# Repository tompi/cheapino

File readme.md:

Cheapino
========

Probably one of the cheapest split keyboards you can build.

This is the result of really enjoying building keyboards,
but not wanting to spend that much money on it.
The pcb is reversible, connected using rj45,
and utilizes a japanese duplex matrix, so only one
mcu is needed. For hotswap I recommend a case(pictured above),
but soldering the switches is of course the cheapest option :)

You want one?
See the [ordering guide](doc/orderingguide.md) for what you need and how to buy it.

See the [build guide v2](doc/buildguide_v2.md) for more details and pictures of how to actually build it.

Some info on the [plate/case solutions](doc/plates_and_cases.md) I know about.

Checkout the [troubleshooting guide](doc/troubleshooting.md) if your Cheapino does not work.

See the [firmware guide](doc/firmware.md) for how to build and customize keyboard firmware.
The cheapino has vial support, or you can build your own QMK to customize EVERYTHING.
Even the onboard RP2040-Zero LED is controllable by QMK...

I added [a few tips and tricks here](doc/tips.md).

[Loads of beautiful build pictures here.](doc/gallery.md)

# License

This work is licensed under a [Creative Commons Attribution license.](LICENSE.txt)

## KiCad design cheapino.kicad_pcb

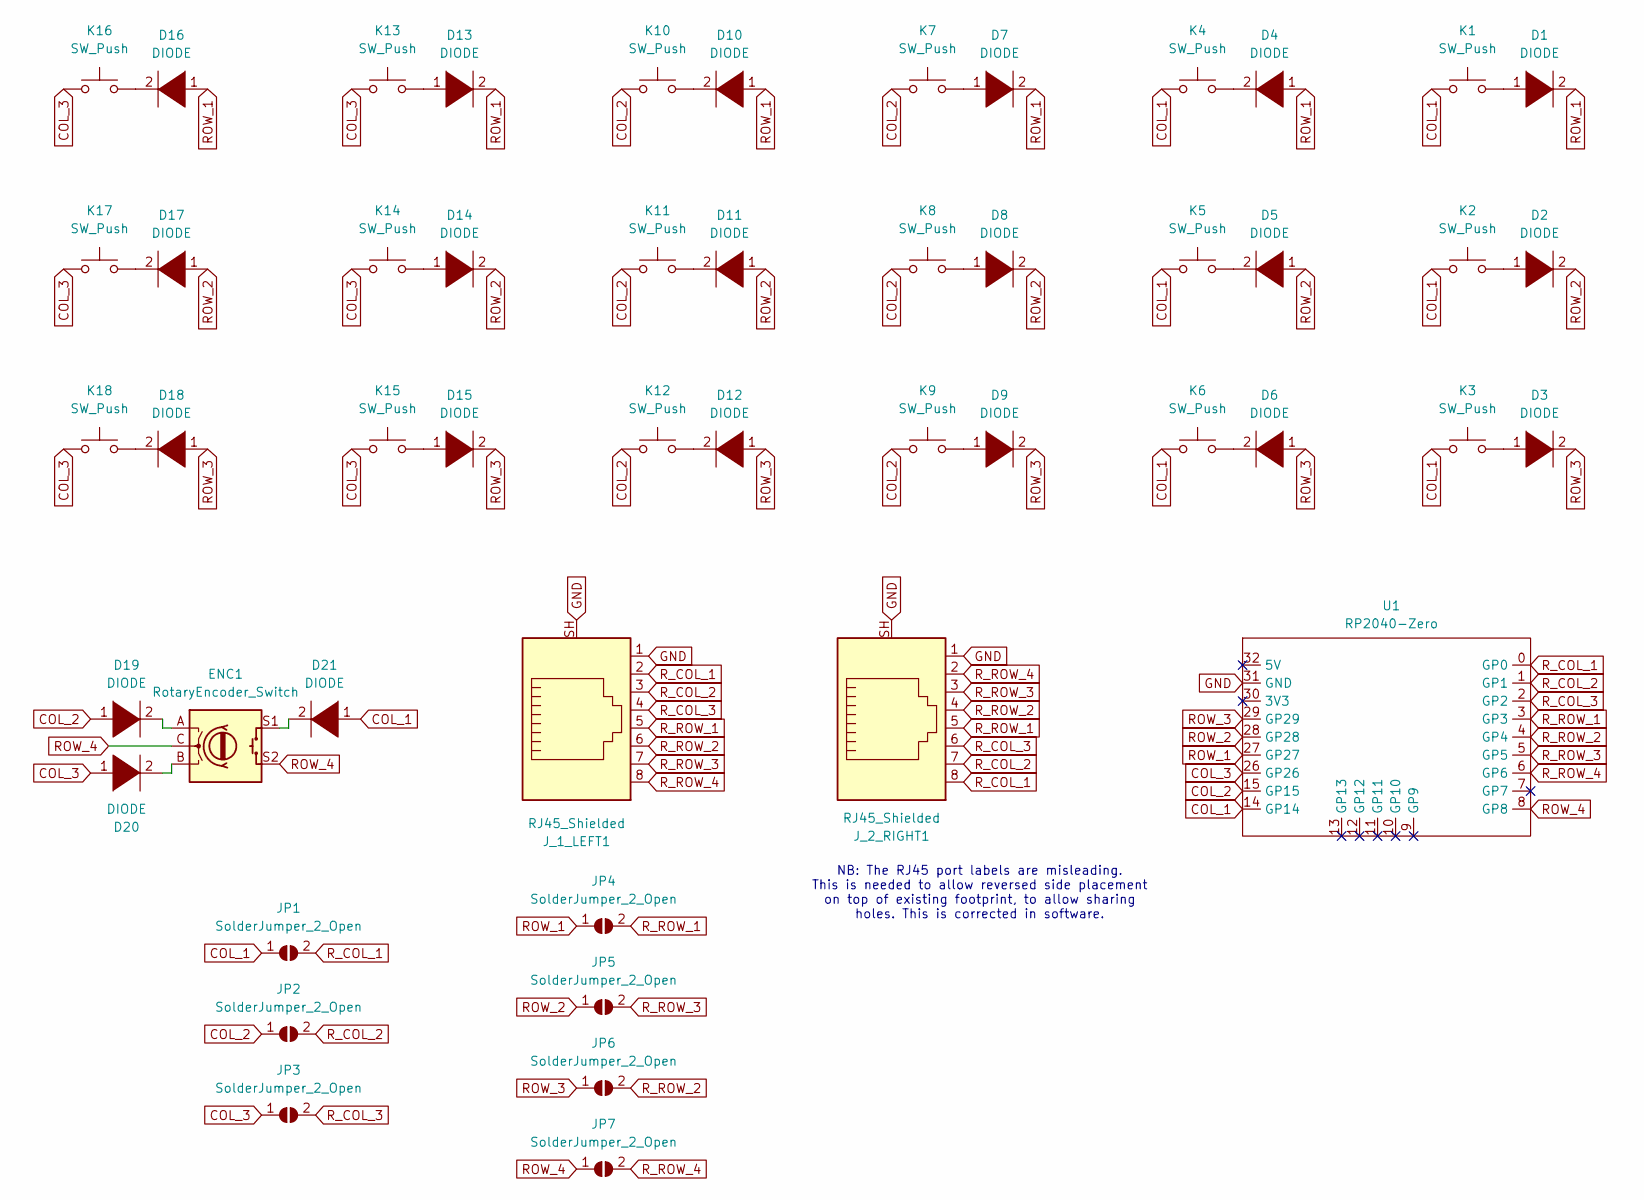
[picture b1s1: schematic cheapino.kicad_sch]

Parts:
D1, D2, D3, D4, D5, D6, D7, D8, D9, D10, D11, D12, D13, D14, D15, D17, D18, D19, D20, D21: DIODE; Diode-dual
D16: DIODE; D_SOD123_axial
ENC1: RotaryEncoder_Switch; RotaryEncoder_Alps_EC11E-Switch_Vertical_H20mm
JP1, JP2, JP3, JP4, JP5, JP6, JP7: SolderJumper_2_Open; SolderJumper-2_P1.3mm_Open_TrianglePad1.0x1.5mm
J_1_LEFT1, J_2_RIGHT1: RJ45_Shielded; RJ45_Ninigi_GE
K1, K2, K3, K4, K5, K6, K7, K8, K9, K10, K11, K12, K13, K14, K15, K16, K17, K18: SW_Push; Kailh_socket_MX_optional_reversible
U1: RP2040-Zero; MCU_RP2040_Zero_34

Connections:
COL_1: D21.1 (K), JP1.1 (A), K1.1, K2.1, K3.1, K4.1, K5.1, K6.1, U1.14 (GP14)
COL_2: D19.1 (K), JP2.1 (A), K7.1, K8.1, K9.1, K10.1, K11.1, K12.1, U1.15 (GP15)
COL_3: D20.1 (K), JP3.1 (A), K13.1, K14.1, K15.1, K16.1, K17.1, K18.1, U1.26 (GP26)
GND: J_1_LEFT1.1, J_1_LEFT1.SH, J_2_RIGHT1.1, J_2_RIGHT1.SH, U1.31 (GND)
unnamed: D1.1 (K), K1.2
unnamed: D2.1 (K), K2.2
unnamed: D3.1 (K), K3.2
unnamed: D4.2 (A), K4.2
unnamed: D5.2 (A), K5.2
unnamed: D6.2 (A), K6.2
unnamed: D7.1 (K), K7.2
unnamed: D8.1 (K), K8.2
unnamed: D9.1 (K), K9.2
unnamed: D10.2 (A), K10.2
unnamed: D11.2 (A), K11.2
unnamed: D12.2 (A), K12.2
unnamed: D13.1 (K), K13.2
unnamed: D14.1 (K), K14.2
unnamed: D15.1 (K), K15.2
unnamed: D16.2 (A), K16.2
unnamed: D17.2 (A), K17.2
unnamed: D18.2 (A), K18.2
unnamed: D19.2 (A), ENC1.A
unnamed: D20.2 (A), ENC1.B
unnamed: D21.2 (A), ENC1.S1
ROW_1: D1.2 (A), D4.1 (K), D7.2 (A), D10.1 (K), D13.2 (A), D16.1 (K), JP4.1 (A), U1.27 (GP27)
ROW_2: D2.2 (A), D5.1 (K), D8.2 (A), D11.1 (K), D14.2 (A), D17.1 (K), JP5.1 (A), U1.28 (GP28)
ROW_3: D3.2 (A), D6.1 (K), D9.2 (A), D12.1 (K), D15.2 (A), D18.1 (K), JP6.1 (A), U1.29 (GP29)
ROW_4: ENC1.C, ENC1.S2, JP7.1 (A), U1.8 (GP8)
R_COL_1: JP1.2 (B), J_1_LEFT1.2, J_2_RIGHT1.8, U1.0 (GP0)
R_COL_2: JP2.2 (B), J_1_LEFT1.3, J_2_RIGHT1.7, U1.1 (GP1)
R_COL_3: JP3.2 (B), J_1_LEFT1.4, J_2_RIGHT1.6, U1.2 (GP2)
R_ROW_1: JP4.2 (B), J_1_LEFT1.5, J_2_RIGHT1.5, U1.3 (GP3)
R_ROW_2: JP6.2 (B), J_1_LEFT1.6, J_2_RIGHT1.4, U1.4 (GP4)
R_ROW_3: JP5.2 (B), J_1_LEFT1.7, J_2_RIGHT1.3, U1.5 (GP5)
R_ROW_4: JP7.2 (B), J_1_LEFT1.8, J_2_RIGHT1.2, U1.6 (GP6)

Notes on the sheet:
NB: The RJ45 port labels are misleading. This is needed to allow reversed side placement on top of existing footprint, to allow sharing holes. This is corrected in software.

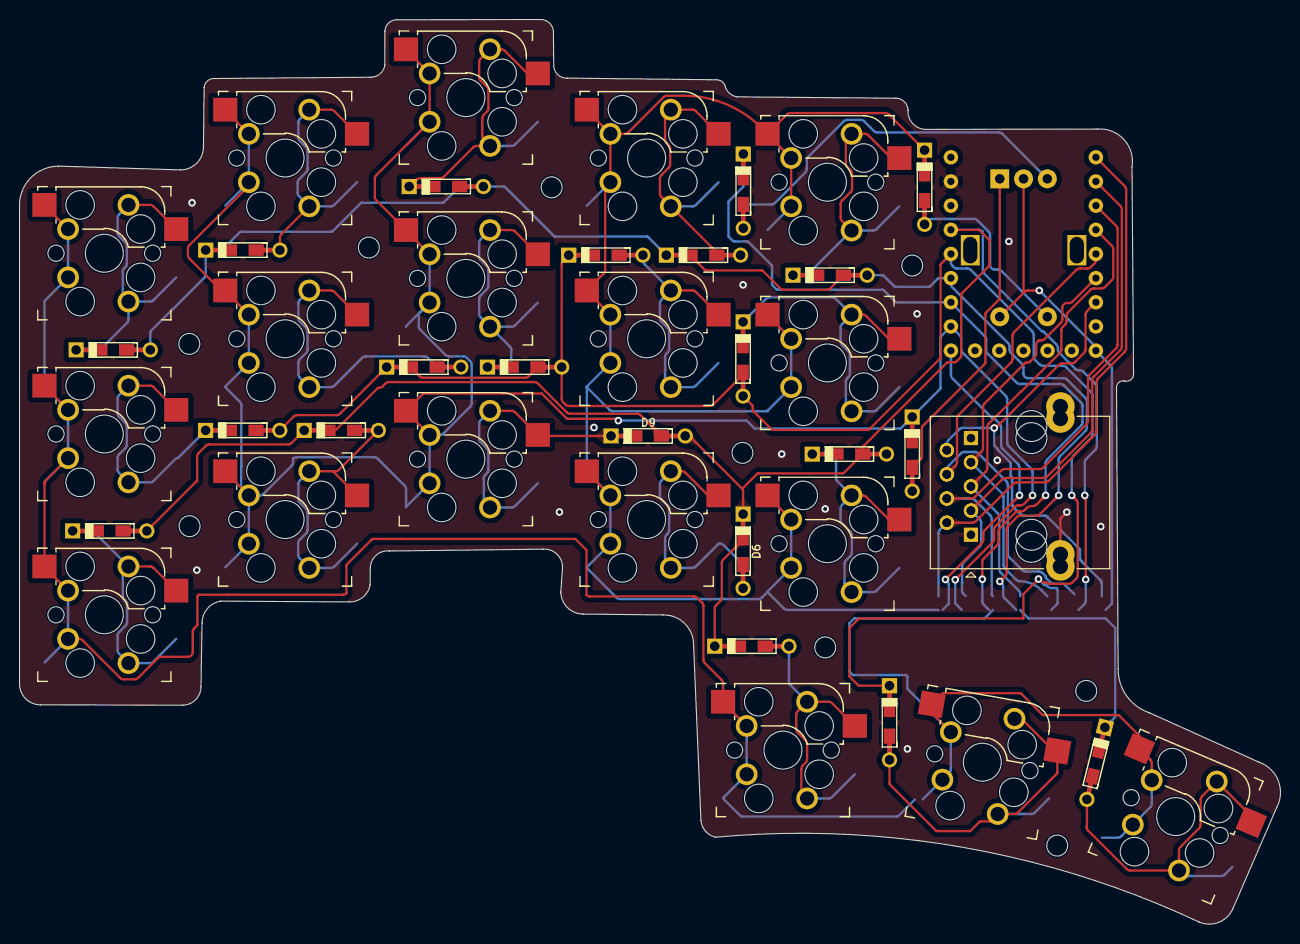
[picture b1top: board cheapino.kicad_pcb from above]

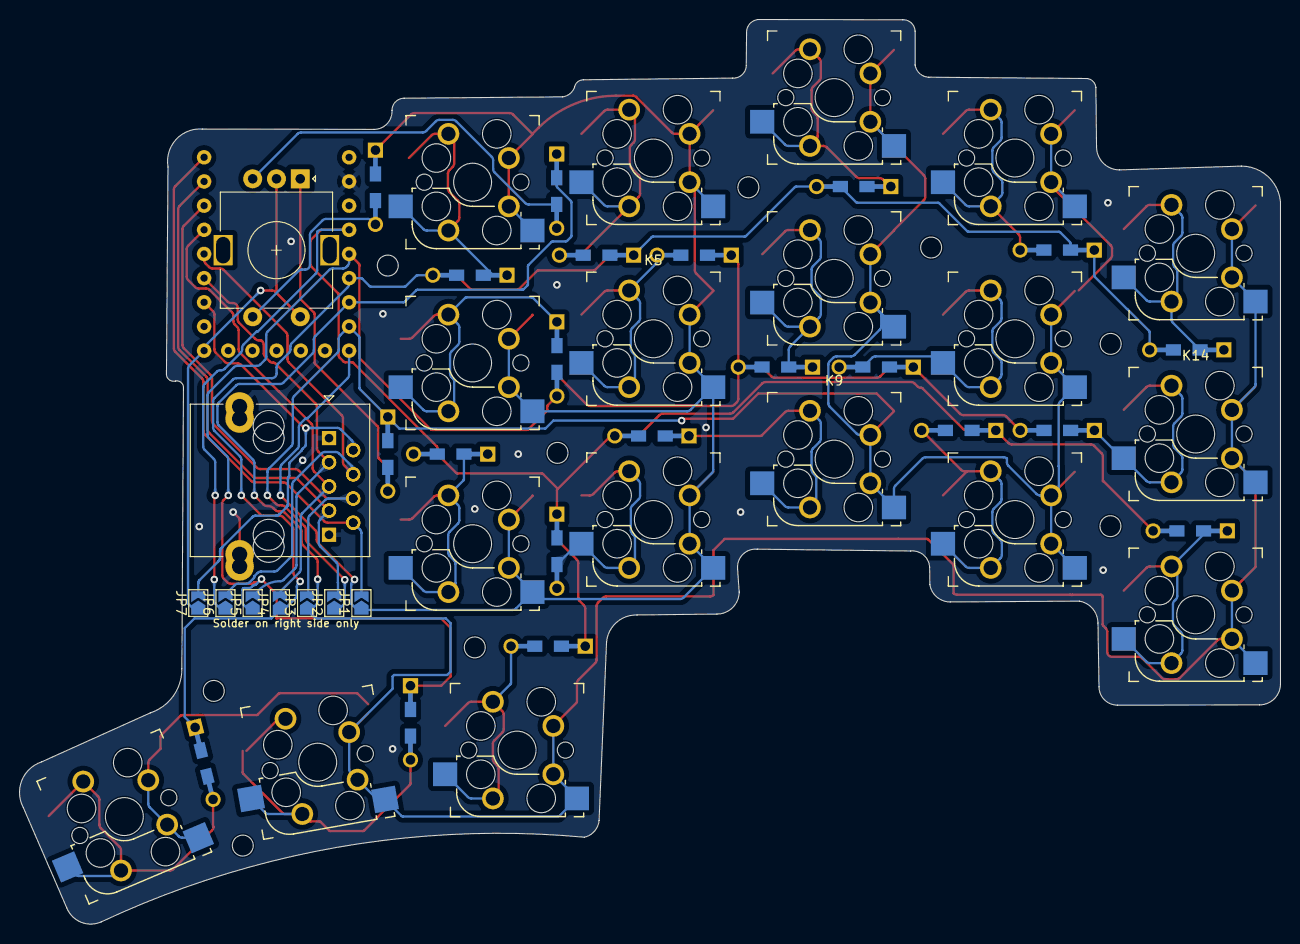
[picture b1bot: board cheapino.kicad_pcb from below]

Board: 2 copper layers, 132.5 x 95.1 mm, 50 parts (9 on the bottom side), 36 nets.

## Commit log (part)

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2023-01-22 passes drc
2023-01-28 Rev 1, ordered from jlcpcb
2023-01-30 1.1: Rounded tracks and teardrops
2023-03-26 Fixed missing pads on one smb diode
2023-03-26 Readme and some images
2023-03-31 changed image
2023-04-29 Build guide for v1
2023-04-29 Fix links
2023-05-08 Add contributed images to build guide
2023-05-08 Typo in links
2023-05-08 Add another build
2023-07-19 Two new builds added
2023-07-26 Added another build
2023-07-26 Fix broken image
2023-07-26 Added miryoku flash instructions
2023-08-02 Addded link to case by Chaccroon
2023-08-02 Text change
2023-08-10 Added a build, and updated build guide to recommend covering up possible gnd short
2023-09-21 add plate
2023-10-08 Hotswap support and solder jumpers
2023-11-04 V2 First draft
2023-11-11 Reversible optional hotswap, move the eth port further
2023-11-11 actually changed pcb
2023-11-11 add teardrop
2023-11-12 add mounting holes + plate with mounting
2023-11-15 Ordered prototype
2023-11-20 M2 Mounting holes
2023-12-16 Fix missing SMD footprint on right/back Diodo D16
2023-12-16 Fixes #10 Added some mounting holes
    Also added logo, rounded tracks and tear drops
2023-12-27 Initial draft of case: wip
2023-12-28 Case: wip
2023-12-30 Add picture from finex
2024-01-29 Add a few pics and close #15
2024-01-29 Add wooden tenting pic
2024-02-18 Move pictures into images folder
2024-02-18 Firmware setup/build guide
2024-02-18 Correct spelling and link fw from mainpage
2024-03-01 Fix embarassing missing trace for column 2...
2024-03-13 Fix number of diodes required
2024-03-14 Fixes #23: fw guide typo
2024-03-16 Added logo copper layer, removed some labels
    This commit was ordered from jlcpcb
2024-03-21 Troubleshooting guide
2024-03-21 Fix missing image in troubleshooting guide
2024-04-01 Elaborate on encoder customization
    As suggested by jinchoung
2024-04-01 Link to @MrBarbie 3D printed fork in the build guide
    Close #27
2024-04-06 Add note about v2 being released on front page.
    Also add remark about 3D printed fork on front page
2024-04-07 Add information about vial configuration
2024-04-18 v2 building and ordering guide
2024-04-18 Fix formatting errors and add image
2024-04-19 Adding soldering pads step to build guide
2024-04-21 Updated vial info and added v2 image on fp
2024-04-21 Fix image link
2024-04-21 Some more firmware comments
2024-04-26 Add vial web description and more dfu details
2024-04-28 Plates with standoffs and beginning of a case
2024-04-29 Case wip
2024-05-01 Case v2 wip
2024-05-01 Case, wip
2024-05-08 Update orderingguide.md to say PCB is reversible
2024-05-10 Added info about hotswap sockets
2024-05-11 Image of hotswap and suggested hotswap before diodes
2024-05-11 Update v2 socket to show v2 mcu socketed
2024-05-11 Some cases and info
2024-05-18 scad bottom plate wip
2024-05-19 Right bottom prototype done
2024-05-23 Removed magsafe insert and adjusted one wrongly placed column
2024-05-28 Printing top left
2024-05-28 Add 3D printed case link
2024-06-05 Case bug-fixes
    * Too small mounting hole inserts
    * 1mm too high top offset
    * 0.5 larger top case to avoid too tight fit
2024-06-08 Top-right, finished first prototype
    Will print tuesday...
2024-06-09 Add a notice about Miryoku support
    https://github.com/tompi/cheapino/issues/41
2024-06-09 Fix space for solder bridges
2024-06-14 Fix space and broken url in ordering guide
2024-06-18 Version on thingiverse
2024-06-20 Some case info
2024-06-22 Moved pcb files into separate folder.
    Also added some images/links to v2 case
2024-06-22 Rotated image
2024-06-23 More v2 images and case info
2024-07-07 Slightly increase the size of the RJ45 hole in the case
    Widening the RJ45 connector hole along the x-axis by 0.45mm makes it
    easier to fit the assembled board without sanding.
2024-07-24 Fix silicone bumper ali link
    Fix #43
2024-07-25 Added some tips/tricks
    Fixes #35
2024-08-11 Slightly larger diode slots
2024-08-11 Slightly larger tolerance for top case
2024-08-19 Add link to some nifty cables
2024-08-19 Added pics of nice case builds
2024-08-21 Make RJ45 case cutout slightly larger
    The fit was so tight I broke a connector on a case...
2024-08-21 Make RJ45 case cutout slightly larger
    The same change as last, except for the top right now
2024-08-21 Rotate top right same as left
2024-08-24 More images...
2024-09-07 Case build guide
2024-09-07 Added warning about magnetic cable, ref #64
2024-09-07 Expanding on the virtues of socketing MCU
    Also added some troubleshooting items
2024-09-13 add case build pictures and description
2024-09-13 add picture to readme.md
2024-09-13 Add pics and update md file
2024-09-13 add missing pic
2024-09-14 Added new build picture
2024-09-14 Added some firmware tips and links
2024-09-24 Expanded diode cutouts and recentered
    Also explained which openscad version to use
2024-10-06 Add troubleshooting for #78
2024-10-06 Added usb 3.2 cable warning(#78) on ordering guide also
2024-10-06 Add more miryoku customization info. Fixes #84
2024-10-07 Fix #75
2024-10-07 Add soldering guide, ref #85
2024-10-07 2 more pics
2024-10-07 Specify type of legs needed per socket also in the build guide
2024-10-07 More images
2024-10-13 Troubleshooting routes
2024-10-13 Add link to interactive schematic
2024-10-13 Added missing encoder columns in debugging tool
2024-10-30 Some more pics
2024-11-10 Fixes #52
2024-11-23 Remove lock file
2024-11-23 Default to v2 in firmware guide, ref #104
2024-11-24 Fix bug in interactive schematics
2024-11-25 refactor: remove trailing whitespace
2024-11-25 refactor: fix typos
2024-11-26 Update master file for interactive schematics
2024-12-03 feat(case): MCU and RJ45 cover
2024-12-03 perf(case): faster preview
2024-12-03 feat(case): RJ45 cover
2024-12-03 feat(case): MCU cover
2024-12-03 feat(case): make the cover rounded
2024-12-03 fix(case): keep the original case
2024-12-14 refactor(case): use global variable for cover radius
2024-12-21 Nicenano wireless top left draft
2024-12-22 Increase hotswap cutout to support Gateron sockets
    Was customized to Kailh before, and Gateron didnt fit...
2024-12-22 Modularized and split some files
2024-12-23 fix(case): rotate in slicer
    Rotating the design early causes confusion for many print services,
    as they may mistakenly assume it represents the intended orientation for use.
2024-12-23 fix(case): keycap doesn't fit
2024-12-27 Add 0.4mm screw clearance.
2024-12-27 Increase clearance around encoder.
2024-12-27 Update model.
2024-12-28 lowered the bumper position bellow the encoder on the bottom cases increased the depth of the enconder holes on the bottom cases
2024-12-28 removed unwanted config
2024-12-28 normalized import
2025-01-06 fix(case): deeper hole for encoder clamp
2025-01-06 fix(case): faster preview
2025-01-18 Increased hotswap cutouts to also fit otemu sockets
2025-01-21 Smaller step
2025-01-21 Add license: fix #116
2025-01-22 Add local license copy, ref #116
2025-01-26 Remove low profile socket from ordering guide.
    This socket seems to create a lot of problems.
    (suspect thick legs needed require more heat and might break mcu...)
    Also replaced broken diode link
2025-03-24 Suggest more spacious case as mentioned in #131
2025-04-20 Added warnings/troubleshooting about magnetic cables
    As described in #130
2025-04-21 Added images. Fixes #128 #136
2025-04-22 Fix wrong image link
2025-04-24 Top and bottom PCB plates
2025-04-24 Remove top plate schematic
2025-04-24 Unhide random value label
2025-05-21 Increase hotswap sockets and move encoder cutout
2025-05-22 Add build scripts
2025-05-22 Revert top plate design to thinner outline
2025-05-22 Documentation
2025-07-23 PCB Blueprint Advice & RJ45 Improve Spec
    Added a note about how the white outlines/blueprint of the PCB work. Also added a note for the RJ45 socket to make it more accurate.
2025-12-31 Fix #156
2026-03-15 Added minimal plate, as requested in #165
